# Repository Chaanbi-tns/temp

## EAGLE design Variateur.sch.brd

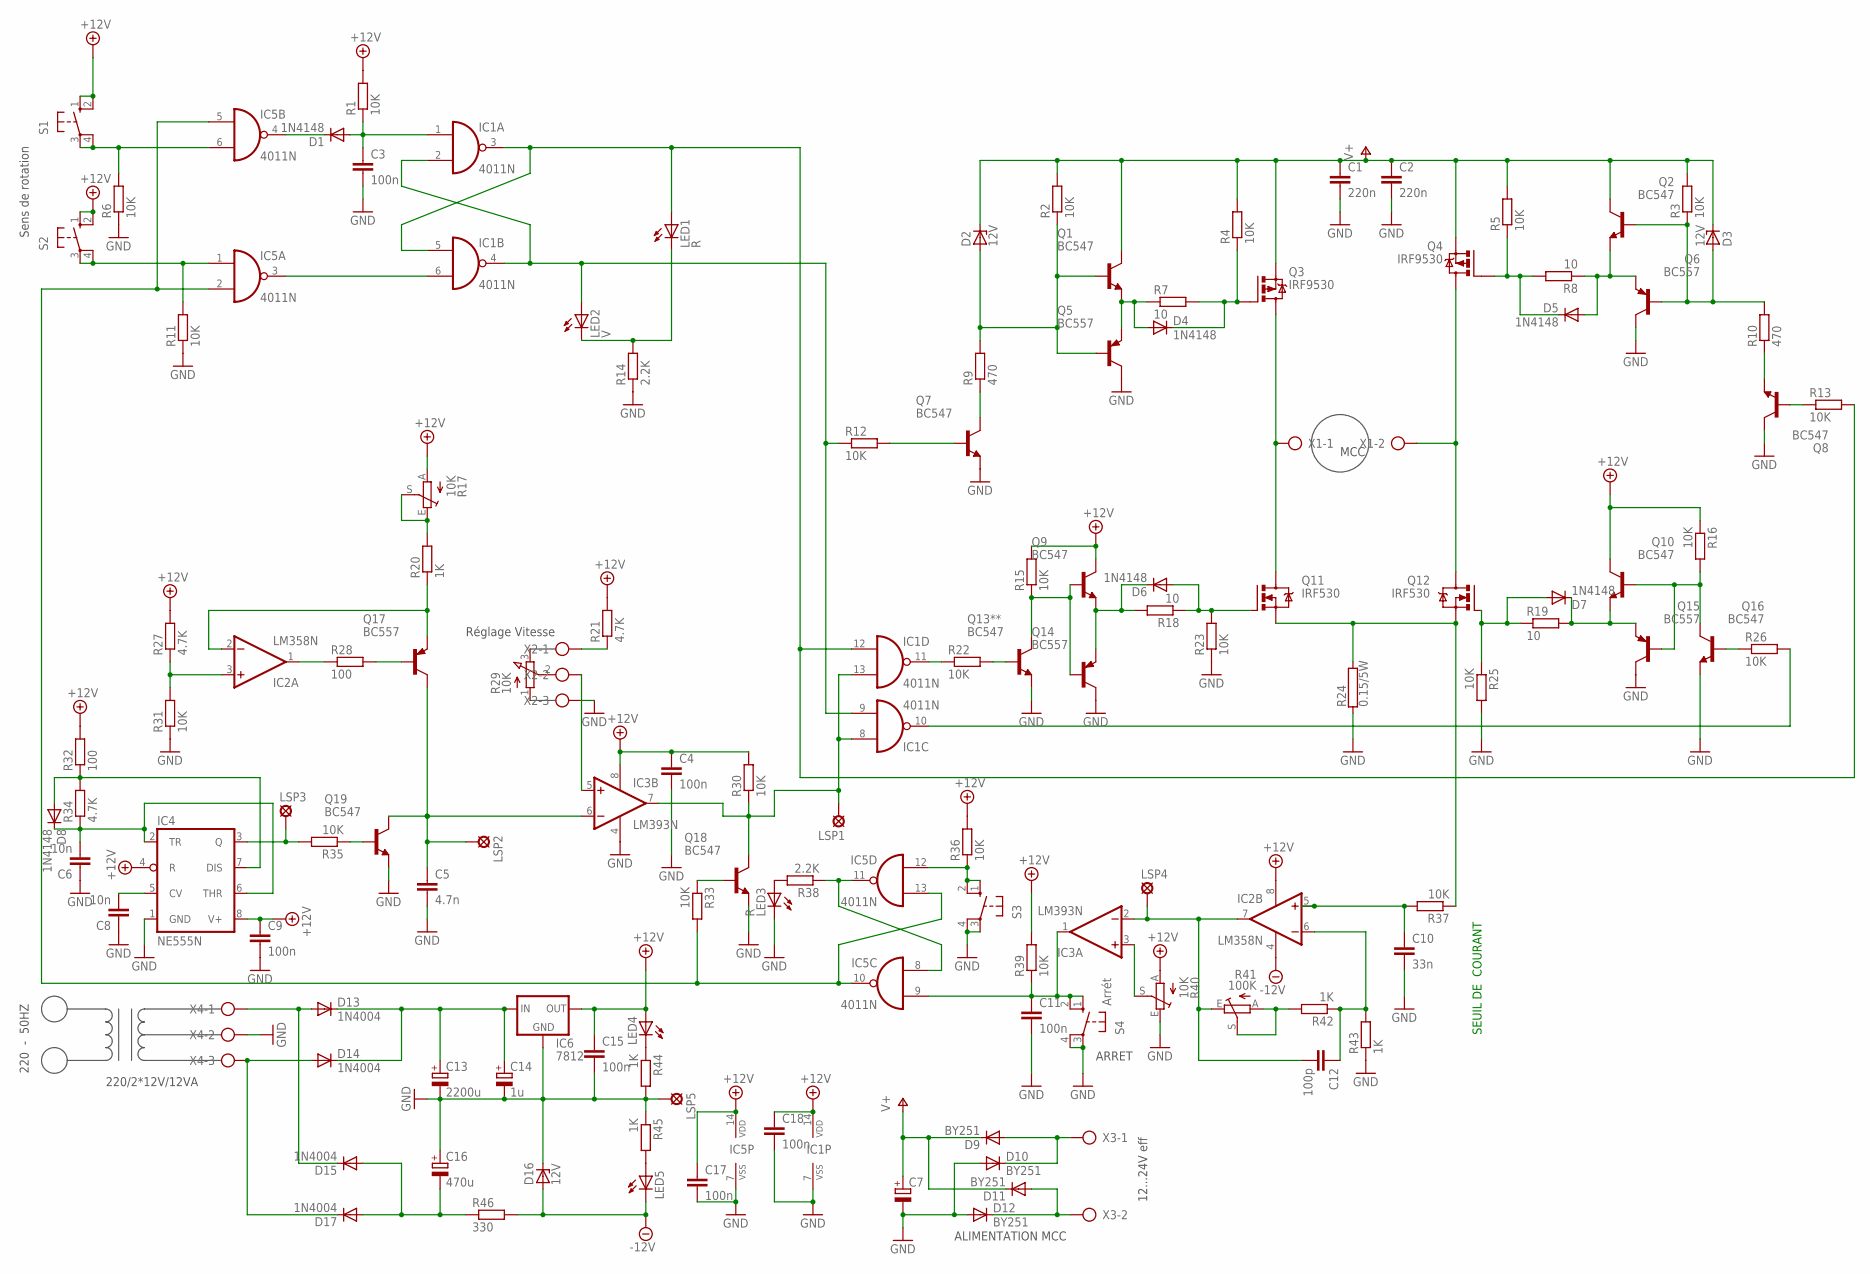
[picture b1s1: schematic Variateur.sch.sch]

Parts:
C1, C2: 220n; C150-064X183
C3, C4, C9, C11, C15, C17, C18: 100n; C050-035X075
C5: 4.7n; C050-035X075
C6, C8: 10n; C050-035X075
C7: CPOL-EUE10-25; EB25D
C10: 33n; C050-035X075
C12: 100p; C050-035X075
C13: 2200u; E5-13
C14: 1u; E2,5-6
C16: 470u; E3,5-10
D1, D4, D5, D6, D7, D8: 1N4148; DO35-10
D2, D3, D16: 12V; DO41Z10
D9, D10, D11, D12: BY251; DO201-15
D13, D14, D15, D17: 1N4004; DO41-10
IC1, IC5: 4011N; DIL14
IC2: LM358N; DIL08
IC3: LM393N; DIL08
IC4: NE555N; DIL08
IC6: 7812; 78XXS
LED1, LED3: R; LED5MM
LED2: V; LED5MM
LED4, LED5: LED5MM
LSP1, LSP2, LSP3, LSP4, LSP5: LSP10
Q1, Q2, Q7, Q8, Q9, Q10, Q13**, Q16, Q18, Q19: BC547; TO92
Q3, Q4: IRF9530; TO220BV
Q5, Q14: BC557; TO92-EBC
Q6, Q15: BC557; TO92
Q11, Q12: IRF530; TO220BV
Q17: BC557; TO92-CBE
R1, R2, R3, R4, R5, R6, R11, R16, R23, R25, R30, R31, R33, R35, R36, R37, R39: 10K; 0207/10
R7, R8, R18, R19: 10; 0207/10
R9, R10: 470; 0207/10
R12, R13, R15, R22, R26: 10K; 0207/15
R14: 2.2K; 0207/15
R17, R40: 10K; LI10
R20, R42, R43, R44, R45: 1K; 0207/10
R21, R27, R34: 4.7K; 0207/10
R24: 0.15/5W; HPS923
R28, R32: 100; 0207/10
R29: 10K; 3RP/1610N
R38: 2.2K; 0207/10
R41: 100K; LI10
R46: 330; 0207/10
S1, S2, S3: 40-XX; B3F-40XX
S4: Arrét; B3F-40XX
X1, X3: AK300/2
X2, X4: AK300/3

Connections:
+12V: C4.1, C9.1, C15.1, C17.1, C18.1, IC1.14 (VDD), IC2.8 (V+), IC3.8 (V+), IC4.4 (R), IC4.8 (V+), IC5.14 (VDD), IC6.OUT, LED4.A, Q9.3 (C), Q10.3 (C), R1.2, R15.2, R16.1, R17.A, R21.2, R27.2, R30.2, R32.2, R36.2, R39.2, R40.A, S1.1 (S), S1.2 (S1), S2.1 (S), S2.2 (S1)
-12V: D16.A, IC2.4 (V-), LED5.K (C), R46.2
D12: D11.A, D12.C, X3.2
GND: C1.2, C2.2, C3.2, C4.2, C5.2, C6.1, C7.-, C8.1, C9.2, C10.2, C11.2, C13.-, C14.-, C15.2, C16.+, C17.2, C18.2, D10.A, D12.A, D16.C, IC1.7 (VSS), IC3.4 (V-), IC4.1 (GND), IC5.7 (VSS), IC6.GND, LED3.K (C), LSP5.MP, Q5.C, Q6.3 (C), Q7.1 (E), Q8.3 (C), Q13**.1 (E), Q14.C, Q15.3 (C), Q16.1 (E), Q18.1 (E), Q19.1 (E), R6.1, R11.1, R14.1, R23.1, R24.1, R25.2, R31.1, R40.E, R43.1, R44.2, R45.1, S3.3, S3.4 (P1), S4.3, S4.4 (P1), X2.3, X4.2
unnamed: C8.2, IC4.5 (CV)
unnamed: D7.A, Q12.G, R19.1, R25.1
unnamed: Q11.S, Q12.S, R24.2, R37.1
unnamed: Q19.2 (B), R35.1
unnamed: D8.A, IC4.7 (DIS), R32.1, R34.2
unnamed: D13.A, D15.C, X4.1
unnamed: D14.A, D17.C, X4.3
unnamed: LED4.K (C), R44.1
unnamed: C6.2, D8.C, IC4.2 (TR), IC4.6 (THR), R34.1
unnamed: C13.+, C14.+, D13.C, D14.C, IC6.IN
unnamed: C16.-, D15.A, D17.A, R46.1
unnamed: LED5.A, R45.2
unnamed: C5.1, IC3.6 (-IN), LSP2.MP, Q17.C, Q19.3 (C)
unnamed: IC5.8 (I0), IC5.11 (O), R38.1
unnamed: C12.2, IC2.7 (OUT), IC3.2 (-IN), LSP4.MP, R41.E
unnamed: R41.A, R41.S, R42.2
unnamed: IC4.3 (Q), LSP3.MP, R35.2
unnamed: R17.E, R17.S, R20.2
unnamed: Q17.B, R28.2
unnamed: IC2.1 (OUT), R28.1
unnamed: IC2.3 (+IN), R27.1, R31.2
unnamed: LED3.A, R38.2
unnamed: IC2.2 (-IN), Q17.E, R20.1
unnamed: IC5.2 (I1), IC5.5 (I0), IC5.10 (O), IC5.13 (I1), R33.2
unnamed: IC3.5 (+IN), X2.2
unnamed: R21.1, X2.1
unnamed: IC1.8 (I0), IC1.13 (I1), IC3.7 (OUT), LSP1.MP, Q18.3 (C), R30.1
unnamed: Q18.2 (B), R33.1
unnamed: IC5.12 (I0), R36.1, S3.1 (S), S3.2 (S1)
unnamed: C10.1, IC2.5 (+IN), R37.2
unnamed: C11.1, IC3.1 (OUT), IC5.9 (I1), R39.1, S4.1 (S), S4.2 (S1)
unnamed: IC3.3 (+IN), R40.S
unnamed: Q8.1 (E), R10.1
unnamed: IC1.11 (O), R22.1
unnamed: Q13**.2 (B), R22.2
unnamed: IC1.10 (O), R26.2
unnamed: D6.C, Q9.1 (E), Q14.E, R18.2
unnamed: Q9.2 (B), Q13**.3 (C), Q14.B, R15.1
unnamed: D6.A, Q11.G, R18.1, R23.2
unnamed: IC1.2 (I1), IC1.4 (O), IC1.9 (I1), LED2.A, R12.1
unnamed: Q7.2 (B), R12.2
unnamed: Q7.3 (C), R9.1
unnamed: D2.A, Q1.2 (B), Q5.B, R2.1, R9.2
unnamed: D4.A, Q1.1 (E), Q5.E, R7.1
unnamed: Q3.D, Q11.D, X1.1
unnamed: D4.C, Q3.G, R4.1, R7.2
unnamed: Q4.D, Q12.D, X1.2
unnamed: C12.1, IC2.6 (-IN), R42.1, R43.2
unnamed: D5.C, Q4.G, R5.1, R8.2
unnamed: D7.C, Q10.1 (E), Q15.1 (E), R19.2
unnamed: Q16.2 (B), R26.1
unnamed: Q8.2 (B), R13.1
unnamed: IC1.3 (O), IC1.5 (I0), IC1.12 (I0), LED1.A, R13.2
unnamed: Q10.2 (B), Q15.2 (B), Q16.3 (C), R16.2
unnamed: D3.A, Q2.2 (B), Q6.2 (B), R3.1, R10.2
unnamed: D5.A, Q2.1 (E), Q6.1 (E), R8.1
unnamed: LED1.K (C), LED2.K (C), R14.2
unnamed: C3.1, D1.A, IC1.1 (I0), R1.1
unnamed: IC1.6 (I1), IC5.3 (O)
unnamed: D1.C, IC5.4 (O)
unnamed: IC5.1 (I0), R11.2, S2.3, S2.4 (P1)
unnamed: IC5.6 (I1), R6.2, S1.3, S1.4 (P1)
R: D9.A, D10.C, X3.1
V+: C1.1, C2.1, C7.+, D2.C, D3.C, D9.C, D11.C, Q1.3 (C), Q2.3 (C), Q3.S, Q4.S, R2.2, R3.2, R4.2, R5.2

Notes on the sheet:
SEUIL DE COURANT
MCC
ALIMENTATION MCC
220/2*12V/12VA
220 - 50HZ
Réglage Vitesse
12...24V eff
ARRET
Sens de rotation

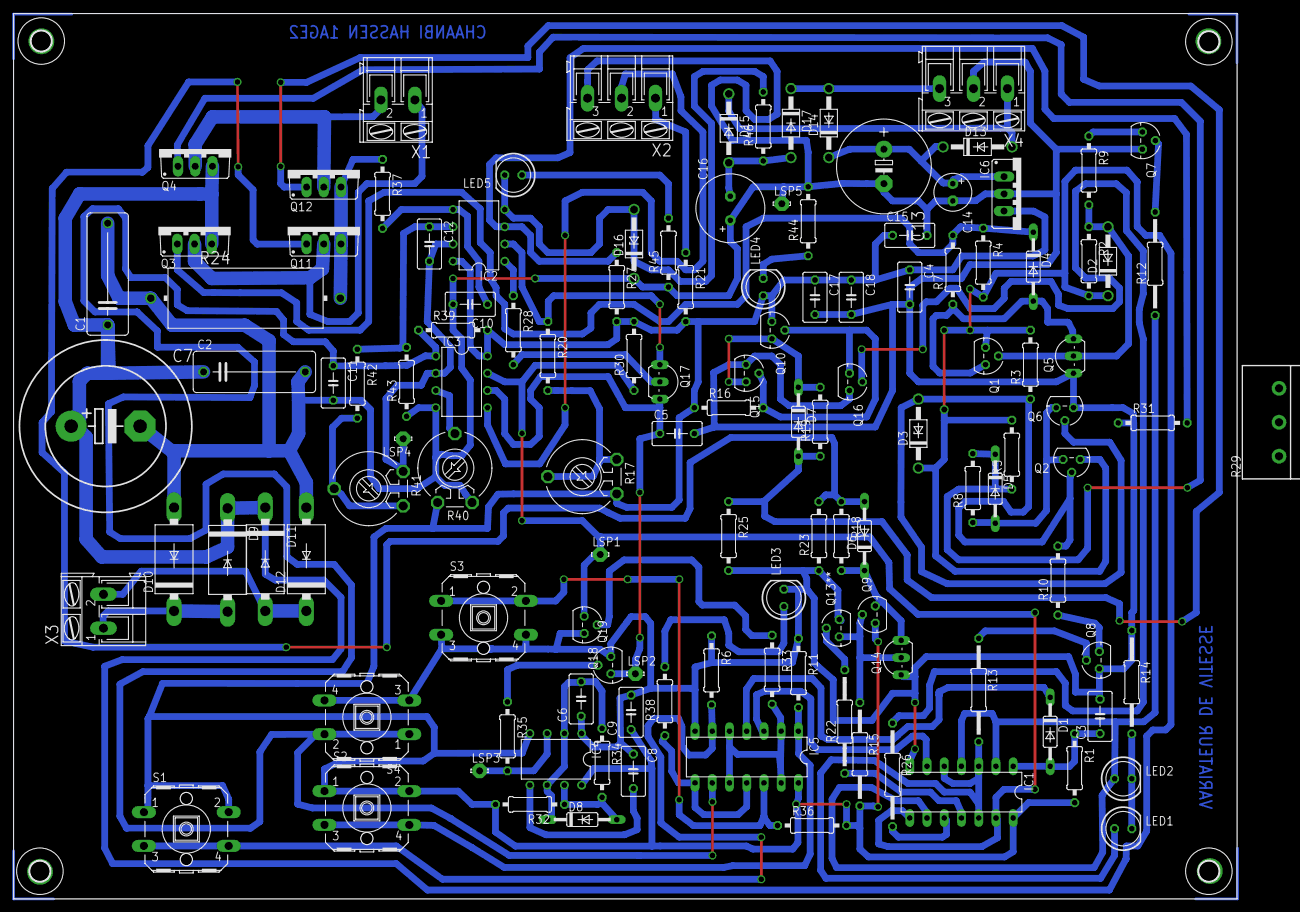
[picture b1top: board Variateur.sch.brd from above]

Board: 2 copper layers, 180.3 x 130.5 mm, 128 parts (0 on the bottom side), 68 nets.

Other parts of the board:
U$1, U$2, U$3, U$4: 3,0

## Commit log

2025-07-24 Create temp
